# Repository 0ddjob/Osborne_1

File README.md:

# Osborne Model 1
## [ROMs](/ROM)
- [2732] Original Osborne BIOS vers. 1.40 (from my Osborne)
- [2732] Original Osborne BIOS vers. 1.43
- [2732] Original Osborne BIOS vers. 1.44 (latest)
- [2732] 3rd party Micro Management OZROM 1E (thanks to user [nelgin](https://forum.vcfed.org/index.php?threads/osborne-1-screen-flash.1245908/post-1400583) on VCFED Forums)
- OZROM manual (cleaned up version thanks to VCFED user booboo)
- [2764] Combined OCC v1.44 & OZROM (requires daughterboard below)
- [2716] Original Osborne character generator ROM (from my Osborne)
- [2716] Original Osborne Screen Pac BIOS Rev. A

Differences between ROM v1.4 and v1.44 include:
```
; CBOOT - added seek 10 tracks and home drive
; GKEY - fixed bell bug
; SENDEN - changed the number of retrys to NRETRY
; PSEKC - added disk head settle delay
; SELDRV - changed start up delay to 500 ms
```
### OCC v1.4 ROM

### OCC Character Generator ROM

### Micro Management OZROM

## [Daughterboard](/2732-to-2764)
[29-Aug-2024: tested successfully]  
ROM daughterboard to accomodate 28-pin 2764 (8KByte) EPROM in the Osborne's 24-pin 2732 (4KByte) BIOS socket.  Idea is to allow switching between the official Osborne ROM and the 3rd party OZROM.  

Address pin A12 is pulled high by the 10KΩ resistor (so default is upper ROM address range 0x1000 to 0x1FFF) or can be switched to ground via a strapping or switch connected to the A12 pin header (so lower ROM address range 0x0000 to 0x0FFF).

## [Using A Gotek](/Gotek)
Big thanks to [Dave Dunfield](http://dunfield.classiccmp.org/index.htm) for the original ImageDisk-format (IMD) disk images.

How to tell if an Osborne 1 disk image is single density (SD) or double density (DD)?

Both disk formats have 40 tracks:
* SD disks have ten 256 byte sectors per track (2560 bytes/track) -> 92KByte formatted capacity
* DD disks have five 1024 byte sectors per track (5120 bytes/track) -> 184KByte formatted capacity

Example output of ```fsed.cpm``` info command on an IMG disk image:
```
              Sector length: 1024
           Number of tracks: 40
          Sectors per track: 5
```
## [EXMON Video Output](/EXMON)
Photos of the EXMON video output shunt.

* Sullins MP-0100-10-DS-4 card edge connector
* Hyko K688-DI - this appears to combine horizontal & vertical sync with the video output, powered by +12V

## [Double Density Upgrade](/DD_Upgrade)
Photos of the original Osborne DD upgrade board and details of a modern reproduction board.

## [Screen Pac Upgrade](/Screen_Pac/)
Photos of the Screen Pac board.

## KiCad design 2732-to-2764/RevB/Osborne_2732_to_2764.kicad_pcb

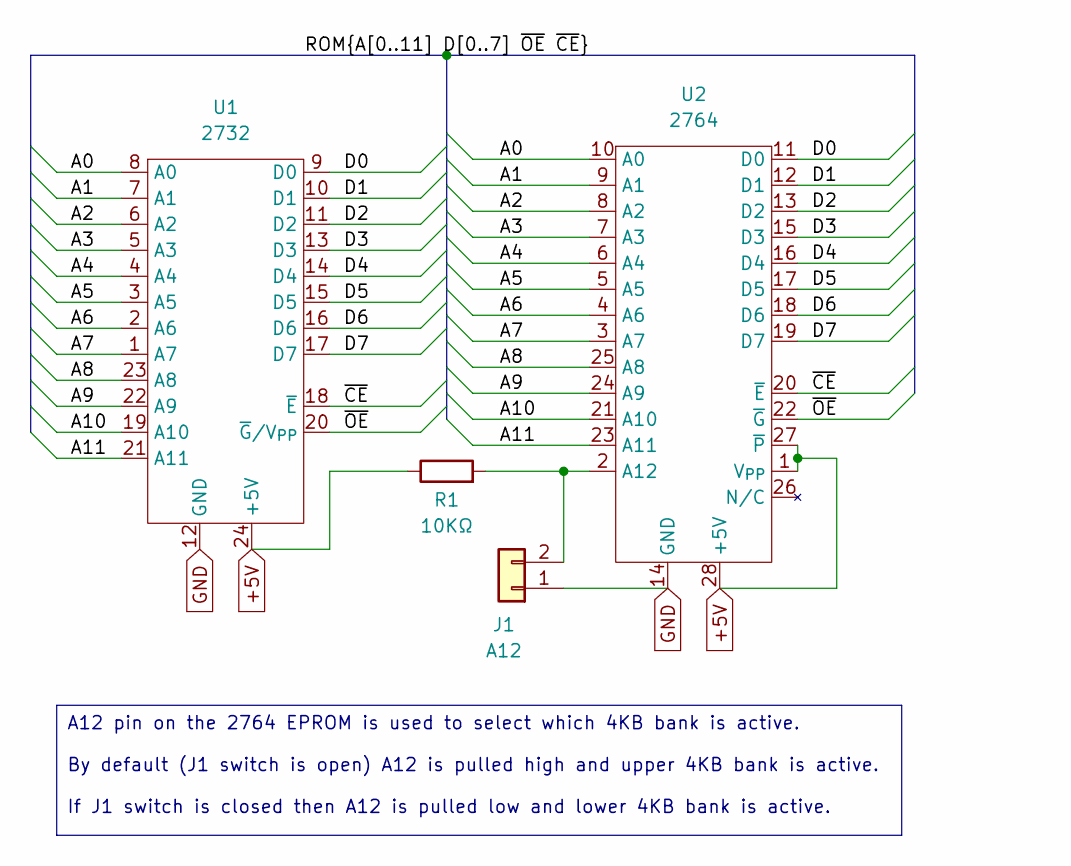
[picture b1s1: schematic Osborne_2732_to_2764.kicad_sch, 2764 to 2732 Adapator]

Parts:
J1: A12; PinHeader_1x02_P2.54mm_Vertical
R1: 10KΩ; R_Axial_DIN0207_L6.3mm_D2.5mm_P2.54mm_Vertical
U1: 2732; DIP-24_W15.24mm-Notch
U2: 2764; DIP-28_W15.24mm_Socket

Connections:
+5V: R1.1, U1.24 (+5V), U2.1 (V_{PP}), U2.27 (~P), U2.28 (+5V)
/A0: U1.8 (A0), U2.10 (A0)
/A1: U1.7 (A1), U2.9 (A1)
/A2: U1.6 (A2), U2.8 (A2)
/A3: U1.5 (A3), U2.7 (A3)
/A4: U1.4 (A4), U2.6 (A4)
/A5: U1.3 (A5), U2.5 (A5)
/A6: U1.2 (A6), U2.4 (A6)
/A7: U1.1 (A7), U2.3 (A7)
/A8: U1.23 (A8), U2.25 (A8)
/A9: U1.22 (A9), U2.24 (A9)
/A10: U1.19 (A10), U2.21 (A10)
/A11: U1.21 (A11), U2.23 (A11)
/D0: U1.9 (D0), U2.11 (D0)
/D1: U1.10 (D1), U2.12 (D1)
/D2: U1.11 (D2), U2.13 (D2)
/D3: U1.13 (D3), U2.15 (D3)
/D4: U1.14 (D4), U2.16 (D4)
/D5: U1.15 (D5), U2.17 (D5)
/D6: U1.16 (D6), U2.18 (D6)
/D7: U1.17 (D7), U2.19 (D7)
/~CE: U1.18 (~E), U2.20 (~E)
/~OE: U1.20 (~G/V_{PP}), U2.22 (~G)
GND: J1.1, U1.12 (GND), U2.14 (GND)
unnamed: J1.2, R1.2, U2.2 (A12)

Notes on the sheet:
A12 pin on the 2764 EPROM is used to select which 4KB bank is active. By default (J1 switch is open) A12 is pulled high and upper 4KB bank is active. If J1 switch is closed then A12 is pulled low and lower 4KB bank is active.

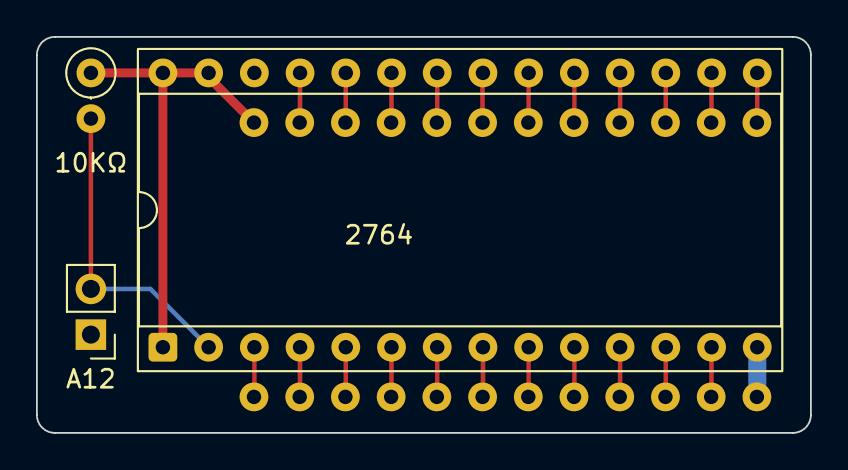
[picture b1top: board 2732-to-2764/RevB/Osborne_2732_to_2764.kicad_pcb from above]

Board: 2 copper layers, 43.0 x 22.0 mm, 4 parts (0 on the bottom side), 25 nets.

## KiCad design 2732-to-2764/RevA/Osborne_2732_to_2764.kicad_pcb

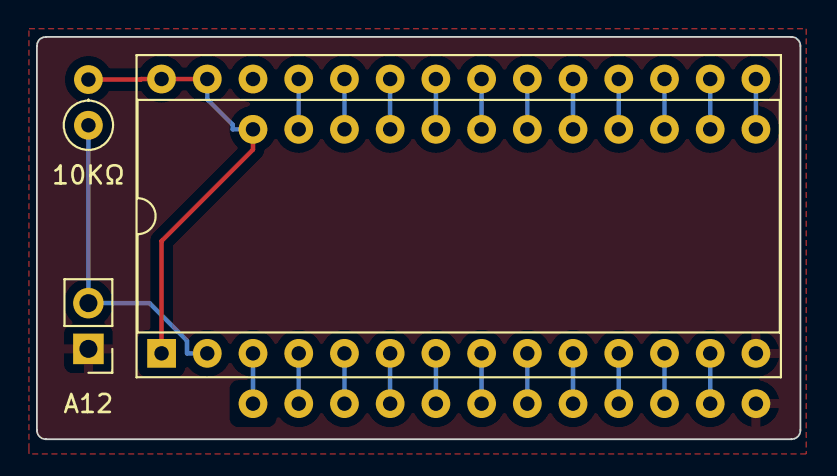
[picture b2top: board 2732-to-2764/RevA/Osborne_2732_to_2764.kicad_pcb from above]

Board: 2 copper layers, 42.4 x 22.4 mm, 4 parts (0 on the bottom side), 25 nets.

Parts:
J1: 2732_ROM_Socket; DIP-24_W15.24mm-Notch
J2: 2764; DIP-28_W15.24mm_Socket
J3: A12; PinHeader_1x02_P2.54mm_Vertical
R1: 10KΩ; R_Axial_DIN0207_L6.3mm_D2.5mm_P2.54mm_Vertical

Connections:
A00: J1.8, J2.10
A01: J1.7, J2.9
A02: J1.6, J2.8
A03: J1.5, J2.7
A04: J1.4, J2.6
A05: J1.3, J2.5
A06: J1.2, J2.4
A07: J1.1, J2.3
A08: J1.23, J2.25
A09: J1.22, J2.24
A10: J1.19, J2.21
A11: J1.21, J2.23
D0: J1.9, J2.11
D1: J1.10, J2.12
D2: J1.11, J2.13
D3: J1.13, J2.15
D4: J1.14, J2.16
D5: J1.15, J2.17
D6: J1.16, J2.18
D7: J1.17, J2.19
GND: J1.12, J2.14, J3.1
unnamed: J2.2, J3.2, R1.1
VCC: J1.24, J2.1, J2.27, J2.28, R1.2
~CE: J1.18, J2.20
~OE: J1.20, J2.22

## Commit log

2024-08-15 Added ROMs
2024-08-16 Added ROM pictures
2024-08-16 Resized pictures
2024-08-19 Converted IMD -> HFE disk images
2024-08-19 Added FF configuration files for simplicity
2024-08-19 Intial 2764 adaptor design
2024-08-19 Corrected subdirectory name
2024-08-19 Updated silkscreen
2024-08-21 Corrected Gerbers for PCBWAY (still pending testing)
2024-08-21 Added v1.44 source from FOG CP/M disk 008
2024-08-22 Source code cleanup
2024-08-23 Updated socket pins
2024-08-23 Moved image
2024-08-23 Resized image
2024-08-23 Cleaned-up OZROM manual thanks to booboo
2024-08-29 Tested daughterboard
2024-09-15 Added photos of EXMON adaptor
2024-09-15 Soldered EPROM directly to daughterboard
2024-09-15 Further device detail
2024-10-13 Added DD upgrade details
2024-11-25 Updated to Kicad 8.0.6
2025-04-21 Added Screen Pac upgrade info
2025-04-21 Redrew/improved schematic
    Created symbols for the 2732 & 2764 EPROMs and used busses to connect.
    PCB is roughly identical - connections are all the same but I manually doubled 5V rail track width
